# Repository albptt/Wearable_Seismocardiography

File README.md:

<h1 align="center"> HEA </h1>

   <br> 
   <br> 
   
## Getting Started
### Clone the repository
Run the command on your terminal at the desired location:
```
git clone git@github.com:ltebs-polimi/AY2324_I_Project-6.git
```
### Dependencies
It is recommended to create a virtual environment to run the GUI. This can be done by running on your terminal:
```
python -m virtualenv GUI_venv
```
The latest versions of these libraries should then be installed within the virtual environment:
- ```PyQt5```
- ```numpy```
- ```scipy```
- ```pandas```
- ```openpyxl```
- ```pyqtgraph```
- ```os```
- ```sys```
- ```time```
- ```logging```
- ```struct```
## Filetree
Directories are organized as follows:
```
││├───CASE
│││   └──STL files
│││
││├───GUI
│││   ├──pyqt5_venv
│││   └──GUI.py
│││
││├───PCB
│││   ├──HEA.bdr
│││   └──HEA.sch
│││
││└───PSoC_code
││    ├──Oled-Psoc5
││    └──Stream mode.cydsn
││       │
││       ├───Generated_Source
││       │   └───PSoC5
││       └───TopDesign
││
│└───Validation_Study
│    ├──Output_Measurements
│    └──Plots
│
└───Images

```
   
## Intro
The aim of the present project is to develop a wearable device for the continuous monitoring of the heart rate, using the seismocardiography tecnique. 
  
### Seismocardiography
Continuous cardiac monitoring is necessary for the diagnosis of cardiovascular diseases. Medical emergencies caused by cardiac arrests can be prevented by a continuous cardiac monitoring, which can be easily provided by a wearable device. [^1]

Seismocardiography consists in the extraction of the heart rate value from the measurement of the vibration of the chest caused by the contraction of the heart, the closure of the cardiac valves and the ejection of the blood into the vascolature. [^1]  This term appeared in literature for the first time in the 90's. Vibrations induced by the cardiac activity are mainly correlated to valve closure (heart sounds) and cardiac systole. In particular, seismocardiographic movements at relatively low frequency reflect the recoil forces that results from the contraction of the heart muscle when it ejects blood into the vessels. These forces are responsible for body accelerations in the order of 5 mg. [^2]
  
Failing at reaching the same performances of other well established measurement techniques for the heart rate, seismocardiography didn't find a wide usage in the clinical practice. However, in the last 20 years, thanks to the development brought to the inertial sensors field by MEMS technology, this technique has been at the center of several studies. [^2] Appropriate sensors for seismoardiography are acceleroemeters and IMUs (6 axes accelerometer-gyroscope or 9 axes accelerometer-gyroscope-magnetometer). [^1] Studies present in literature investigated the usage of both single sensors and multiple sensors combined together, and vary in the site of measurement and type of processing utilized. 
  
With the spread of wearable devices and the lowering in their prices, it becomes important to further study the application of cheap and miniaturized sensors to perform biosignal analysis.
Accelerometers and ECG electrodes are common sensors inserted in smart garments such as T-shirts for the monitoring of the athlete performance and smart pajamas for the assessment of the quality of sleep. One of the main objectives in this field is the reduction in the number of the sensors needed to extract the wanted information. Limiting the electronics reduces both the production and the maintenance costs and simplifies the design of such garments. 

Most of the studies present in literature use just one accelerometer as sensor to study the heart rate acquisition in static conditions. Some more recent studies proposed the usage of a second accelerometer to measure the accelerations at the chest level not caused by the cardiac contraction, in order to remove motion artefacts that are superimposed to the heart signal and to make the tecnique effective even in conditions of light movement. [^3]
  
### Heart attack
The proposed solution is a device called "Heart attack" or "HEA" in short. It uses a single 3 axes accelerometer positioned on the chest in contact with the skin, connected through wires to a unit that can be worn on the belt or on the side with a shoulder strap, and that both provides a first interface with the user and manages the communication with a pc. A graphical user interface shows on a pc the result of the measurement and makes the utilizer able to connect and operate with the device. In short, the device records the data relative to the acceleration of the chest of the user and sends it to a pc that has previously been connected to the device throught the appropriate software. The processing of the raw data and the computation of the heart rate value is performed on the pc. Then, the extracted HR value is both sent back to the device, which uses it to manage the peripherals, and displayed on the pc screen both numerically and through a real-time plot. 

The initial solution aimed to incorporate the use of two accelerometers, but during the development process, it was decided to opt for a single accelerometer. This choice yielded satisfactory results while maintaining the simplicity and cost-effectiveness of the device in a hypothetical industrial context.
  
The details of the project are discussed in the following sections:
- [Hardware](#hardware)
- [Firmware](#firmware)
- [Communcation](#communication)
- [Processing](#processing)
- [Graphical user interface](#graphical-user-interface)
- [Acquisition Protocol](#acquisition-protocol) 
- [Clinical validation study](#clinical-validation-study) 
- [Limitations and future developments](#limitations-and-future-developments)

   <br> 
   
## Hardware
### Reference Folder: `PCB`, `Case_3Dprint`
  
HEA is composed by an accelerometer fixed in position on the chest of the user by a band and inserted in a protective shell, and by a central unit installed into a rigid case that can be worn on the belt, thanks to a clip, or on the side thanks to a shoulder strap.  

<br> 

<div align="center">

</div>
  
<br>
  
The electronic circuit has been simulated in breaboard before designing the PCB.   
The electronical components used for the main module are: 
- Psoc 5LP, accelerometer LIS3DH, bluetooth module HC-O6, OLED screen ElectroPeak 0.96'', RBG led, buzzer, 9V alkaline battery, switch, linear voltage regulator LM7805, resistors (220Ω 2x, 330Ω 4x, 1KΩ 4x, 10KΩ 2x), capacitor 100μF.
  
<br>  

<div align="center">

</div>
  
<br>
  
A reset circuit has been added to the main module in order to automatically reset the microcontroller every time the device is turned on.
The electronical components used for the reset circuit are: 
- Dual Operational Amplifier LMx58 Low-Power, resistors (220Ω 1X, 330Ω 1X, 10KΩ 1x), capacitor 470μF.
  
<br>  

<div align="center">

</div>

 <br> 
  
### Hardware functioning discussion:
- The accelerometer and the OLED screen communicate with the microcontroller via I2C, whereas the bluetooth module communicates via UART.
- The accelerometer has also a connection between its interrupt pin and a pin of the microcontroller, so that it can trigger an interrupt when the FIFO register is full. 
- The oled screen shows the name of the device on power on. After 5 seconds it switches to a second window that shows the heart rate value and battery level over time. When the streaming is ongoing, the OLED screen is updated every 5 seconds with the new istantaneous HR value. Every hour the battery level is sampled, this event triggers also an update of the OLED screen to display the updated battery level. 
- The RGB led communicates information about the connection status of the device. If the device is not connected it flashes a red light, if the device is connected but it is not streaming data it emits a stable green light, if the device is connected and it is streaming data it emits a stable blue light. 
- The buzzer can supply information about the state of the battery and about the heart rate value via an alarm. The alarm is triggered when the heart rate value overcomes 120 bpm (which means that the user is suffering tachycardia) or when the battery goes below 5% (a new battery is needed). The alarm lasts 3 seconds, then it is disabled for 30 seconds, after which, if the triggering condition is still present, it will turn on again. 
- The PSOC 5LP and all the peripherals run on 5V, so the 9V of the battery are reduced and stabilized to 5V by the linear voltage regulator. 
- Resistors are used to limit the current running in the RGB led and to reduce the TX signal sent by the microcontroller to the bluetooth module from 5V to 3.3V, to cope with the HC-06 limitations. 
- The 100μF capacitor grants a constant power supply even in case of spikes in the current request of the circuit. 
- A voltage divider is used to reduce the 9V of the battery to 5V in a proportional way, in order to sample such signal with a pin of the microcontroller connected to an ADC and to use it as indication of the battery residual charge.
- The PCB hosts the passive components (capacitor and resistors) and the headers for the pluggable components, providing a compact platform for all the elements.
- The reset circuit generates a 0V signal that lasts approximately 3 seconds when the device is turned on. This signal is generated at the output of a comparator powered between 5V and ground. The non inverting input of the comparator is connected to the positive terminal of a capacitor which is in series to a resitor. As soon as the device is switched on the capacitor starts to charge, when its voltage overcomes 3V (present at the inverting input of the comparator and generated by a voltage divider) the output of the comparator turns from 0V fo approximately 3.6V, ending the 0V signal. This 0V-2s pulse is sent to the reset pin of the microcontroller. 

### 3D printed case design discussion:
- The 3D printed case is meant to contain the PCB with all the peripherals except for the accelerometer, which is instead encapsulated in a protective shell and worn on the torso, fixed in position by an elastic band. Some windows in the upper panel of the case grant the visibility of the OLED screen and of the RGB led, provide a passage for the accelerometer cables and host the switch. The case can be worn on the belt thanks to a clip or on the side via a shoulder strap. The PCB is screwed inside the case whereas all the other components are glued in position. The cover can be easily removed and placed back in position thanks to velcro straps.

<div align="center">

</div>

<div align="center">

</div>

   <br> 
   
## Firmware
### Reference Folder: `PSoC_code`
The initial configuration state of each peripheral is stored within the EEPROM memory of the PSoC5 device, these are read at each power-on. Namely, the information stored concerns:
- The sentence to be displayed on the OLED screen at startup
- The color shown by the RBG led at startup
- The initial off state of the Buzzer
- The resolution in bit and the full scale in g of the accelerometer data

During normal running conditions, the EEPROM writing occurs only upon receiving a new bit resolution configuration or full-scale configuration, from the GUI, or when the device enters low-power mode, to ensure that the new settings are persistent upon the next power-on. An if statement on the macro `WRITE_EEPROM` is instead implemented for the first EEPROM programming, once done, the macro is set to False.

<br> 

<div align="center">

</div>
  
<br>

Recommended settings for HR measurement are: 10bit resolution and +2/-2g full scale. Entering low-power mode implies reducing the resolution to 8bit.
  
The OLED screen serves the purpose to provide an additional interface for the user and its management relies on an [open source library](https://github.com/NRDaza/Oled-Psoc5). When the device is powered on, the OLED screen shows the name of the device "Heart Attack" for 5 seconds, and then it shows the main window. The main window is composed by the acronym "HEA" at the top, followed by the indication on the current heart rate and by the residual battery charge. The heart rate corresponds to the instantaneous heart rate shown in the GUI and is updated every 5 seconds. On the other hand, the battery is sampled for the first time 5 seconds after powering on, then it is sampled again and updated on the OLED screen every hour. If the battery level is under 5% the sound alarm by the buzzer is turned on for 3 seconds and the device automatically enters in low power mode. The sound alarm is also activated if the measured heart rate exceeds 120bpm, as the device is intended for stationary use. After the 3 seconds, the buzzer undergoes a refractory period of 30 seconds before re-entering the triggerable mode.

The RBG LED is meant to signal the connection status of the device. Initially, while HEA is not yet paired with the laptop, the LED will blink in RED driven by a PWM signal with a period of 1 second and duty cycle of 50%. Successful pairing is then flagged via a fixed green light, while during data streaming a fixed blue light is shown.

<div align="center">

</div>

Accelerometer reading is performed exploiting the integrated 32-level FIFO register. The FIFO is filled at a 50Hz sampling frequency. As the last level is filled, the `OVRN` bit in the `FIFO_SRC_REG` is set HIGH triggering an interrupt service routine. Within the ISR, initial attempts at recovering the data consisted in reading each FIFO level one at a time and reconstructing the acceleration along each axis, before transmitting it via UART protocol to the GUI. Being implemented while using FIFO mode, this approach was faulty and resulted in hundreds of acceleration samples being lost, due to the fact that data collection is stopped until all registers are read and a different mode is selected. 

<br> 

<div align="center">

</div>
  
<br>

For this reason, Stream mode was implemented, in this case when the buffer is full, the FIFO index restarts from the beginning and older data is replaced by the current. To avoid the risk of overwriting samples, the reading procedure was sped up by shrinking the ISR to perform the reading of all the 192 bytes at once and transmitting them raw.

<br> 

<div align="center">

</div>
  
<br>

   <br> 
   
## Communication
### Reference Folder: `PSoC_code`, `GUI`
The visualization on the GUI of the acquired data is possible thanks to the serial communication that connects the microcontroller and the GUI interface via Bluetooth.
The port is automatically detected by clicking the button "Connect" (which triggers the sending of character "v") and waiting for the response from the microcontroller: if the line "Go $$$" is correctly received, then the COM port is open and data streaming can occur. Sending a character from keyboard makes sure that only the wanted device is called, which in this case is redundant dealing with only one device, but it increases the robustness of the application. 

Once the line is received, the GUI is ready to receive the current settings saved in the EEPROM memory of the device; this is done by sending via software the letter "k", whose purpose from the PSoC side is to trigger a case devolved to sending the bit resolution and the g resolution values.

<br> 

<div align="center">

</div>
  
<br>

If the status of the device is connected, then data streaming can occur, depending on the character (or the shortcut) that the user presses: if "Start acquisition" (or CTRL+b), streaming starts, if "Stop acquisition" (or CTRL+f), streaming stops. Of note, the shortcut to stop streaming was changed from CTRL+s to CTRL+f, because CTRL+s was then used to implement data downloading on an excel file (see section GUI for more details). However, the CTRL+f shortcut still enables the sending of the "s" character, which is the one the PSoC recognizes to stop data streaming. 
The management of the possible variables involved in the bidirectional communication between PSoC and GUI is assolved through a "while" cycle, which is active whenever the condition of connected device and correct string received are satisfied. The "while" comprehends a number of "if" conditions equal to the number of possible buffers, distinguishable thanks to their headers, and has a frequency equal to the accelerometer ISR triggering; therefore, at every iteration of the while loop, 32 samples of acceleration are acquired. The acquisition comprehends unpacking the 192 bytes, converting them properly according to the `BIT_RESOLUTION` and `G_RESOLUTION` global variables, and saving them in variables that can be exploited to update the graph. 

The "if" condition involved in data reading is responsible of triggering the processing flag, which starts the processing chain that will be explained in the following section. Among the other steps, the dispatch of the heart rate value that will be streamed on the OLED, is also included.  

The other "if" conditions are devoted to acquire respectively: the eventual data from the second accelerometer, the g resolution, assigned here to `G_RESOLUTION`, the bit resolution, assigned here to `BIT_RESOLUTION`, and the power mode, which allows to set the `LOW_BATTERY` global, and to show an appropriate warning to the user to suggest the substitution of the battery. The `BIT_RESOLUTION` value can toggle between 8 and 10 bits, the `G_RESOLUTION` value can toggle between 2 and 4 g; these values are consistent with the modality in which the accelerometer is used - using its built-in FIFO - and with the typical value ranges of the specific application - seismocardiography. Of note, these values can be set by the user throughout the acquisition through appropriate buttons (which will be described in section GUI); nevertheless, there's a mismatch of 32 samples between the updating on the software and on the firmware, causing that small portion to have inaccurate values; this can be signaled to the user through a proper warning. 

<br> 

<div align="center">

</div>
  
<br>

   <br> 
   
## Processing
### Reference Folder: `GUI`
Different processing strategies have been investigated. Among the ones showing promissing results, the choosen one shows good concordance with the gold standard device used as reference for the wider HR interval. 
The processing of the signal is composed by the following steps: 
  
- A vector containing 1500 samples (corresponding to 30 seconds since the sampling frequency is 50Hz) of the acceleration on the Z axes is the input to the processing chain.
- Rectification is applied to the raw data vector.
- A Butterworth high pass filter of the fourth order with cut off frequency of 18Hz extracts the cardiac sounds from the overall chest perpendicular acceleration signal. [^2]
- The first 100 samples of the resulting vector are removed to clean the distortion introuced by the filter, the remaining samples are rectified.
- The processed signal is normalized with the z-score and then rectified.
- A threshold equal to the 80% of the variance of the energy of the final signal is computed. [^1]
- The function find peaks of the scipy library extracts the peaks showing the closure of the aortic valve (cardiac event that causes the maximal vibration of the chest).
- The HR value is computed as the mean of the time intervals between the detected peaks.
  
<br> 

<div align="center">

</div>
  
<br>

- This processing is applied every time a new group of 32 samples is delivered to the pc (approximately every 0.64 seconds).
- The value of HR istantaneous is updated every 5 seconds and it is computed as the mean of all the HR values computed in the 5 seconds window prior to the update.
- The value of HR mean is updated every 60 seconds and it is computed as the mean of all the HR values computed in the 60 seconds window prior to the update.
  
It is worth mentioning also the following processing which applies a very different approach and that shows good performances in the range 60bpm-80bpm:
- A vector containing 1500 samples of the acceleration on the Z axes is the input to the processing chain.
- The absolute value of such raw data is first denoised by using a Savitzky-Golay filter. In particular this filter extracts the respiratory signal from the raw data, so by subtracting it from the raw data we can already eliminate a big noise component. [^1]
- A Butterworth fitler of the fourth order between 0.6Hz and 3.6Hz eliminates the freqeuncy components that do not contain the heart rate signal. 
- The processed signal is normalized with the z-score. 
- Thanks to a threshold equal to the 80% of the standard deviation of the analyzed signal it is possible to determine the peaks linked to the valve activity. 
- Once the time istants associated with such peaks are extracted, the heart rate value can be computed from the time interval between peaks. 

   <br> 
   
## Graphical user interface
### Reference Folder: `GUI`
The graphical user interface incorporates all the features necessary to communicate with the device in one window.

To ease the connection with the device, the GUI is equipped with a scroll down menu and two buttons: "Scan" and "Connect to port {}". The box contains the list of serial ports that were found after the serial scan at the start of the GUI. In case it was started before the Bluetooth connection was enabled, the button Scan allows to call the serial scan again, thanks to a signal emitted by the SerialScanner class, and to update the list of ports in the combo box. Finally, the Connect button allows the actual connection with the device, only if the COM port is correct and the device sent the correct string. 

The graphical interface includes a dynamic graph window facilitating the visualization of both raw and processed data. 
The plotting commences after an initial 45-second calibration phase initiated by pressing the Start button. Utilizing the PyQtGraph Python library, the plot displays multiples of 32 samples. 
The "ready" and "ready processing" flags in the serial worker are set to 1 upon the availability of new samples. 
Every second, the Main Window, driven by a timer, checks these flags. If they equal one, the acquired samples are passed to the relevant function in the Main Window, plotted, 
and then the flags are reset to 0 until new samples are acquired. 
A button beneath the graph allows users to toggle between visualizing raw and processed data. Additionally, two buttons enable users to select the background color of the plot (light or dark mode) and clear the graph view.

On the right side of the GUI, editable lines allow users to input personal data about subjects. These data are utilized to create filenames when saving files (see details below).

Two LCD displays provide real-time visualization of instantaneous HR and mean HR. The instantaneous HR is updated every 5 seconds to enhance stability in the displayed value. The mean HR is updated every minute, calculated as the average of the last 12 samples of instantaneous HR shown.

The File menu bar encompasses three actions. The first two actions, "Start Acquisition" and "Stop Acquisition", have been previously discussed in the Communication section. 
The third action, "Save Data," enables users to contemporaneously save two Excel files: one containing raw data values and the other containing instantaneous HR values. 
Filenames are generated based on the user-entered data in the editable lines, structured as follows:
- Raw_data = '{name}_{surname}_{age}.xlsx'
- Instantaneous_HR = f'{name}_{surname}_{age}_HR.xlsx'

These files are intended for more robust offline analysis.

The Settings menu bar offers two actions allowing users to select the desired bit resolution and full scale by toggling between the two available values. 
The current values are continuously displayed on the screen.

Any event from the GUI raising an error is manifested to the user in the form of message boxes with informative text. 

   <br> 

## Acquisition Protocol

Before each acquisition, a protocol was formulated and followed to ensure consistency in results, minimizing possible errors and biases that may compromise the quality of data.

The protocol is articulated in the following steps:

__1. Preparation__: 
- Clean the skin where the accelerometer will be attached to ensure proper adhesion and minimize interference from sweat.
- Choose an appropriate location for attachment based on the anatomical characteristics of the subject’s chest.
- If it's possible to feel the heartbeat by lightly touching the protective shell encapsulating the accelerometer, then the positioning is valid.
- Ensure the device is fully charged or has sufficient battery life to support the duration of data collection.
 
__2. Attachment__:
- Securely affix the accelerometer device to the chosen location with the help of another person.
- Double check the fit to ensure the device is sufficiently but not overly tight to avoid discomfort and allow for normal breathing.

__3. Subject Positioning__:

Three conditions were tested:

- __Seated__: the subject is instructed to sit comfortably with their back supported and feet flat on the ground. Arms are resting on a table and the pulse-oximeter to monitor the reference heart rate is applied to the right index finger. HEA is placed on the table as well in front of the subject, cables are lifted to prevent artifacts due to their breathing-induced dragging on the table.
- __Upright__: the subject is standing straight with minimal movement. Again the pulse-oximeter is applied to the right index finger while the hand is resting on a flat surface. HEA is worn in the belt-like fashion ensuring that cables are not constrained by any strap.
- __Lying down__: the subject lies on an even surface in supine position, while the pulse-oximeter is applied to the right index finger. HEA is placed on the subject’s right side with cables passing over the respective arm.
  
__4. Data collection__: 

Once the previous steps are correctly performed and the subject is ready, data streaming from the device is started. Each acquisition was obtained for a duration of 10 minutes and data was collected every 5 seconds, as the OLED display of HEA is updated, or up to the acquisition of 100 samples. 

   <br> 
   
## Clinical validation study
### Reference Folder: `Statistical_Analysis`
In order to assess the quality of the device a small clinical validation study has been performed. 
To assess the applicability of a measuring instrument in a clinical context, it is necessary to evaluate its validity and reliability (intra- and inter-operator). In cases where such an instrument operates without the intervention of an operator, the validity of its measurements remains the major determining parameter.
Therefore, it is essential to compare the new measuring instrument under analysis with one that is already certified and validated, considered the gold standard. If it is proven that the distributions of measurements from the two devices are strongly correlated, and this assertion holds statistical significance, then the validity of the measurements of the new measuring instrument has been demonstrated.
The clinically validated measurement system used as gold standard in the present study is a Pulse Oximeter A340 produced by Aeon Technology.

The first step involves plotting the coupled measurements obtained from both the new instrument and the gold standard reference. From those plots it is possible to qualitatively analyze the trends of the measurements and the presence of possible biases.
Then some basic statistics are computed (error = Hea measurement - Pulse Oximeter measurement): mean error, mean absolute error, maximum absolute error, minimum absolute error, standard deviation of the absolute error, root mean square error. [^1]
The interpretation of those statistics is straight forward: the lower the better. In the current project a deviation of ±5bpm from the measurements of the gold standard device is considered acceptable.

To verify the correlation between the two data distributions, it is first necessary to determine whether these distributions are normal or not. If both distributions are normal, then the Pearson coefficient is used; otherwise, the Spearman rank correlation coefficient is employed. [^4] The normality of data in the case of small sample sizes is assessed using the Shapiro-Wilk test. [^5]
Both quantitative analyses described above have a qualitative counterpart consisting of interpretable graphs: QQ-plot for normality verification and Bland-Altman plot for correlation verification, with the limits of agreement computed as 1.96 * standard deviation of the differences. [^6]
If the calculated validity coefficient exceeds the threshold of 0.7, then the new measuring instrument is considered valid.
An interpretation commonly used for the correlation coefficient is: 0.90 to 1.00 = excellent, 0.70 to 0.89 = good, 0.50 to 0.69 = moderate, 0.30 to 0.49 = low, <0.30 negligible. [^7]
The minimum number of data points for each distribution should be 20 (significance level 0.05 (alpha), power 0.20 (beta), assuming a moderate correlation between measurements). [^8]

Several acquisitions have been performed during the course of the project on different partecipants that varied for gender and chest anatomy. Those acquisitions have been taken under a multitude of settings: static, with slight motion, with wide movements, seated, standing, laying down. Also different sensor positionings over the chest of the patient have been experimented. The various testing conditions determine the bpm range that is explored during the acquisition. Those measurements have been used to reject inadequate processing methods or sensor positionings. In the end, the choosen processing algorithm described in the section "Processing" has been analysed through six acquisitions perfomed on the same subject with the following settings: two seated, two standing, two laying down, all in static conditions and at rest. The acquisition protocol followed is descrived in the section "Acquisition Protocol". 

The following table shows the results of the statistical analysis of the processing algorytm currently implementend in the device. 

<br> 

<div align="center">

</div>
  
<br>

Mean error, MAE, RMSE show results all below the 5bpm target under all three of the different measurements conditions. The correlation has in the end always been computed through the Spearman rank correlation coefficient since the data recorded by the Pulse Oximeter always resulted not normal. Good correlation results are obtained only in the standing position, while in the laying down position and in the seated position not only the results of the coefficient are too low to determine a strong correlation, but they also vary significantly between the two acquisitions. 

From the analysis of the plots below we can see that the high correlation highlighted in the standing acquisitions is linked to the capability of HEA in correctly following the big variations of the heart rate over time, like for example when this one increases or decreases in a continuous way from 75bpm to 85bpm in the "standing" acquisitions. It is also possible to link the worse results got in the other two measurement conditions to the incapability of HEA in showing a stable heart rate value when its variations are in a more limited range, as can be seen both in the "seated" and in the "lying down" acquisitions.

<br> 

<div align="center">

</div>
  
<br>

The Bland-Altman plots show no bias in all the measurements sets with the exception of the first seated axquisition, where for lower HR values HEA tents to underestimate the recorded value. This limitation of the device should be further investigated through more acquisitions. 

<br> 

<div align="center">

</div>
  
<br>

In conclusion, on one hand the results are promising since the computed errors are all below the target error of ±5bpm, on the other hand a more in-depth statistical analysis would be required to assess correctly the correlation between the measurements of the two devices. This would consist in the application of the same approach described in the current chapter, but on a wider database, containing measurements made on a bigger cohort of participants and under a wider range of measurement conditions. 

<br>

## Limitations and future developments

Two main challenges have been identified for the device, the primary being the limited cohort size of partecipants on which the device has been tested, and the second being the requirement of the stillness of the subject to properly estimate heart rate. 

If by testing the device on a wider population the results obtained are subject dependent, a possible solution may involve tailoring the processing algorithms based on individual subject characteristics such as height, weight, age, and sex. By incorporating these variables into the processing framework, the device can potentially yield more accurate and reliable heart rate measurements across a diverse range of users.

To address the second issue, we propose the integration of two accelerometers to enable motion compensation. This approach aims to mitigate the impact of movement on heart rate estimation, thereby enhancing the device's performance in dynamic scenarios.

In conclusion, we believe that the potential solutions identified will improve the device's overall functionality leading to the possibility of integrating it into sensorized garments for everyday monitoring purposes.

*** 

## Authors

- matteo2.mentasti@mail.polimi.it
- alberto.pettenella@mail.polimi.it
- raffaella.salama@mail.polimi.it
- francesca.vacca@mail.polimi.it

<br>

## References
[^1]: H. Lee, H. Lee, and M. Whang, “An enhanced method to estimate heart rate from seismocardiography via ensemble averaging of body movements at six degrees of freedom,” Sensors (Switzerland), vol. 18, no. 1, pp. 1–12, 2018, doi: 10.3390/s18010238.
[^2]: M. Castiglioni, P; Faini, A; Parati, G; Di Rienzo, “Wearable seismocardiography. - MEDLINE® - ProQuest,” pp. 3954–3957, 2007, [Online]. Available: http://search.proquest.com.zorac.aub.aau.dk/medline/docview/68521306/DE9C4DD26AC74FADPQ/3?accountid=8144.
[^3]: L. Luu and A. Dinh, “Artifact noise removal techniques on seismocardiogram using two tri-axial accelerometers,” Sensors (Switzerland), vol. 18, no. 4, 2018, doi: 10.3390/s18041067.
[^4]: Pozzolo P. Coefficiente di correlazione lineare r di Pearson. Published 2020. Accessed June 28, 2022. 
https://paolapozzolo.it/coefficiente-correlazione-statistica-pearson/ 
[^5]: Pozzolo P. La distribuzione normale spiegata semplice. Published 2020. Accessed June 28, 2022. 
https://paolapozzolo.it/distribuzione-normale/ 
[^6]: F. Jacobs, J. Scheerhoorn, E. Mestrom, J. van der Stam, R. Arthur Bouwman, and S. Nienhuijs, “Reliability of heart rate and respiration rate measurements with a wireless accelerometer in postbariatric recovery,” PLoS One, vol. 16, no. 4 April 2021, 2021, doi: 10.1371/journal.pone.0247903.
[^7]: M. M. Mukaka, “Correlation coefficient and its use,” Malawi Med. J., vol. 24, no. September, pp. 69–71, 2012.
[^8]: M. Parati et al., “Video-based Goniometer Applications for Measuring Knee Joint Angles during Walking in Neurological Patients: A Validity, Reliability and Usability Study,” Sensors, vol. 23, no. 4, 2023, doi: 10.3390/s23042232.

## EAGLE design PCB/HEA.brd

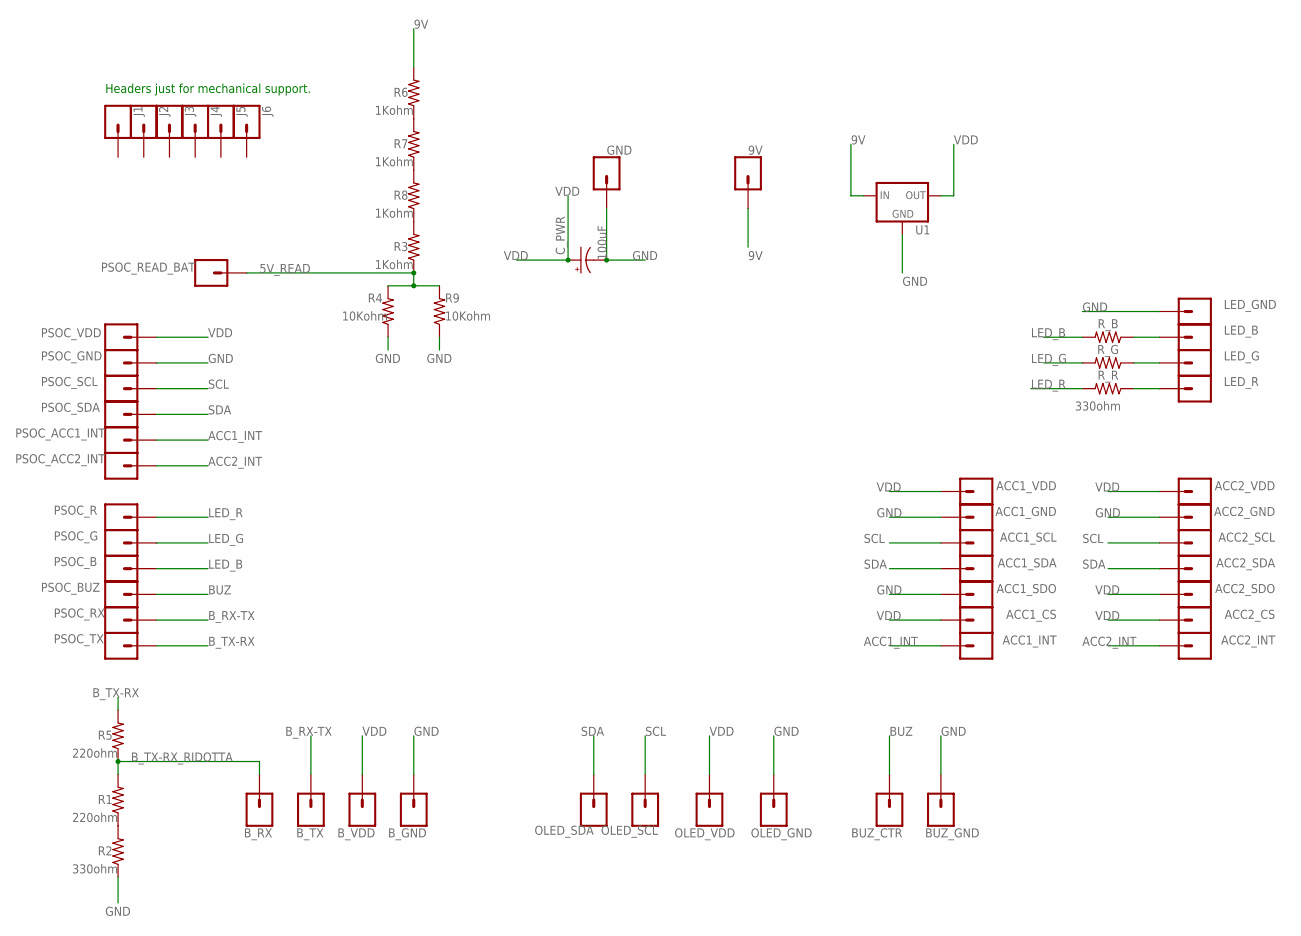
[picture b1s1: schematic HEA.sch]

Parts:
9V: CONN_01; 1X01
ACC1_CS, ACC1_GND, ACC1_INT, ACC1_SCL, ACC1_SDA, ACC1_SDO, ACC1_VDD, ACC2_CS, ACC2_GND, ACC2_INT, ACC2_SCL, ACC2_SDA, ACC2_SDO, ACC2_VDD: CONN_01; 1X01
BUZ_CTR: CONN_01; 1X01
BUZ_GND: CONN_01; 1X01
B_GND: CONN_01; 1X01
B_RX: CONN_01; 1X01
B_TX: CONN_01; 1X01
B_VDD: CONN_01; 1X01
C_PWR: 10uF; CPOL-RADIAL-2.5MM-5MM
GND: CONN_01; 1X01
J1, J2, J3, J4, J5, J6: CONN_01; 1X01
LED_B: CONN_01; 1X01
LED_G: CONN_01; 1X01
LED_GND: CONN_01; 1X01
LED_R: CONN_01; 1X01
OLED_GND: CONN_01; 1X01
OLED_SCL: CONN_01; 1X01
OLED_SDA: CONN_01; 1X01
OLED_VDD: CONN_01; 1X01
PSOC_ACC1_INT, PSOC_ACC2_INT: CONN_01; 1X01
PSOC_B: CONN_01; 1X01
PSOC_BUZ: CONN_01; 1X01
PSOC_G: CONN_01; 1X01
PSOC_GND: CONN_01; 1X01
PSOC_R: CONN_01; 1X01
PSOC_READ_BAT: CONN_01; 1X01
PSOC_RX: CONN_01; 1X01
PSOC_SCL: CONN_01; 1X01
PSOC_SDA: CONN_01; 1X01
PSOC_TX: CONN_01; 1X01
PSOC_VDD: CONN_01; 1X01
R1, R2, R3, R4, R5, R6, R7, R8, R9: AXIAL-0.3
R_B: AXIAL-0.3
R_G: AXIAL-0.3
R_R: AXIAL-0.3
U1: V_REG_78XX-TO-220; TO-220-ALT

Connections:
5V_READ: PSOC_READ_BAT.1, R3.P$1 (1), R4.P$2 (2), R9.P$2 (2)
9V: 9V.1, R6.P$2 (2), U1.IN
ACC1_INT: ACC1_INT.1, PSOC_ACC1_INT.1
ACC2_INT: ACC2_INT.1, PSOC_ACC2_INT.1
BUZ: BUZ_CTR.1, PSOC_BUZ.1
B_RX-TX: B_TX.1, PSOC_RX.1
B_TX-RX: PSOC_TX.1, R5.P$2 (2)
B_TX-RX_RIDOTTA: B_RX.1, R1.P$2 (2), R5.P$1 (1)
GND: ACC1_GND.1, ACC1_SDO.1, ACC2_GND.1, BUZ_GND.1, B_GND.1, C_PWR.2 (-), GND.1, LED_GND.1, OLED_GND.1, PSOC_GND.1, R2.P$1 (1), R4.P$1 (1), R9.P$1 (1), U1.GND
LED_B: PSOC_B.1, R_B.P$2 (2)
LED_G: PSOC_G.1, R_G.P$2 (2)
LED_R: PSOC_R.1, R_R.P$2 (2)
unnamed: R1.P$1 (1), R2.P$2 (2)
unnamed: R3.P$2 (2), R8.P$1 (1)
unnamed: LED_B.1, R_B.P$1 (1)
unnamed: LED_G.1, R_G.P$1 (1)
unnamed: LED_R.1, R_R.P$1 (1)
unnamed: R7.P$1 (1), R8.P$2 (2)
unnamed: R6.P$1 (1), R7.P$2 (2)
SCL: ACC1_SCL.1, ACC2_SCL.1, OLED_SCL.1, PSOC_SCL.1
SDA: ACC1_SDA.1, ACC2_SDA.1, OLED_SDA.1, PSOC_SDA.1
VDD: ACC1_CS.1, ACC1_VDD.1, ACC2_CS.1, ACC2_SDO.1, ACC2_VDD.1, B_VDD.1, C_PWR.1 (+), OLED_VDD.1, PSOC_VDD.1, U1.OUT

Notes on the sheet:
Headers just for mechanical support.

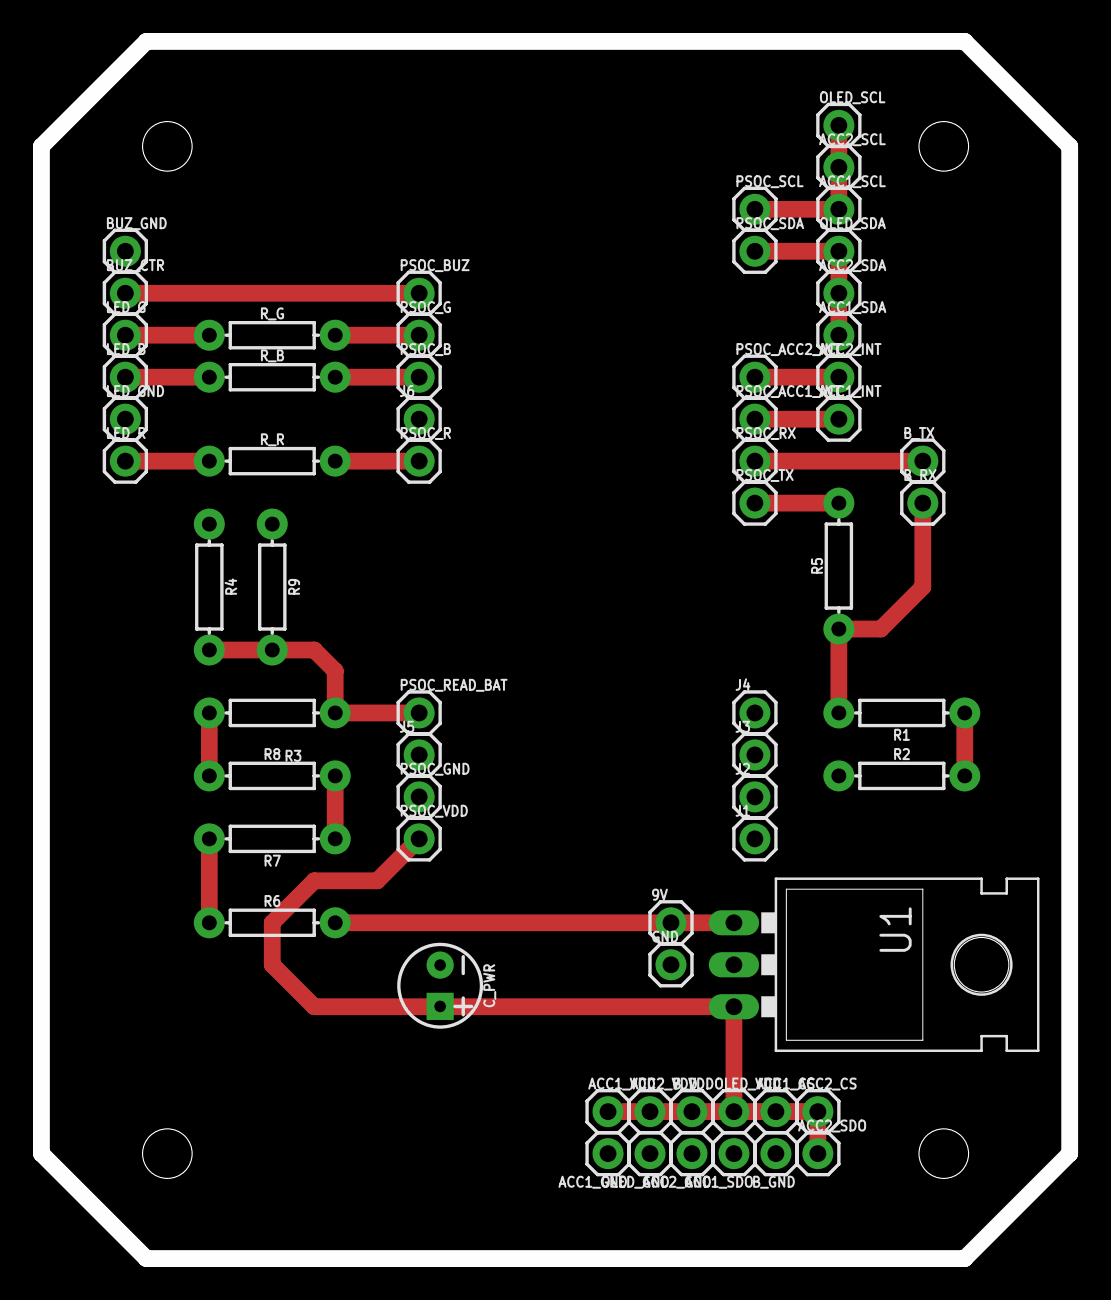
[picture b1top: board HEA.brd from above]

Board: 2 copper layers, 62.2 x 73.7 mm, 63 parts (0 on the bottom side), 22 nets.

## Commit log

2024-02-24 add README
2024-02-24 add CAD
2024-02-24 add GUI
2024-02-24 add images
2024-02-24 add PCB
2024-02-24 add Validation study
2024-02-24 add firmware

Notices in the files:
parts and their libraries:
SparkFun-Connectors: Licensing: Creative Commons ShareAlike 4.0 International - https://creativecommons.org/licenses/by-sa/4.0
